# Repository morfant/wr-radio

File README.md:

# WR-Radio

## 설정 방법

### 1. 첫 실행
```bash
python3 wr-radio.py
```
첫 실행 시 `config.json` 파일이 자동 생성됩니다.

### 2. 스테이션 추가/변경
```bash
nano ~/wr-radio/config.json
```
```json
{
  "stations": [
    {
      "name": "내가 좋아하는 라디오",
      "url": "http://stream-url.mp3",
      "location": "Seoul, Korea",
      "lat": 37.5665,
      "lon": 126.9780,
      "color": [255, 100, 100]
    }
  ]
}
```

### 3. 날씨 기능 (선택)
1. https://openweathermap.org/appid 에서 무료 API 키 발급
2. `config.json`에 키 입력:
```json
   {
     "openweather_api_key": "여기에_키_입력"
   }
```

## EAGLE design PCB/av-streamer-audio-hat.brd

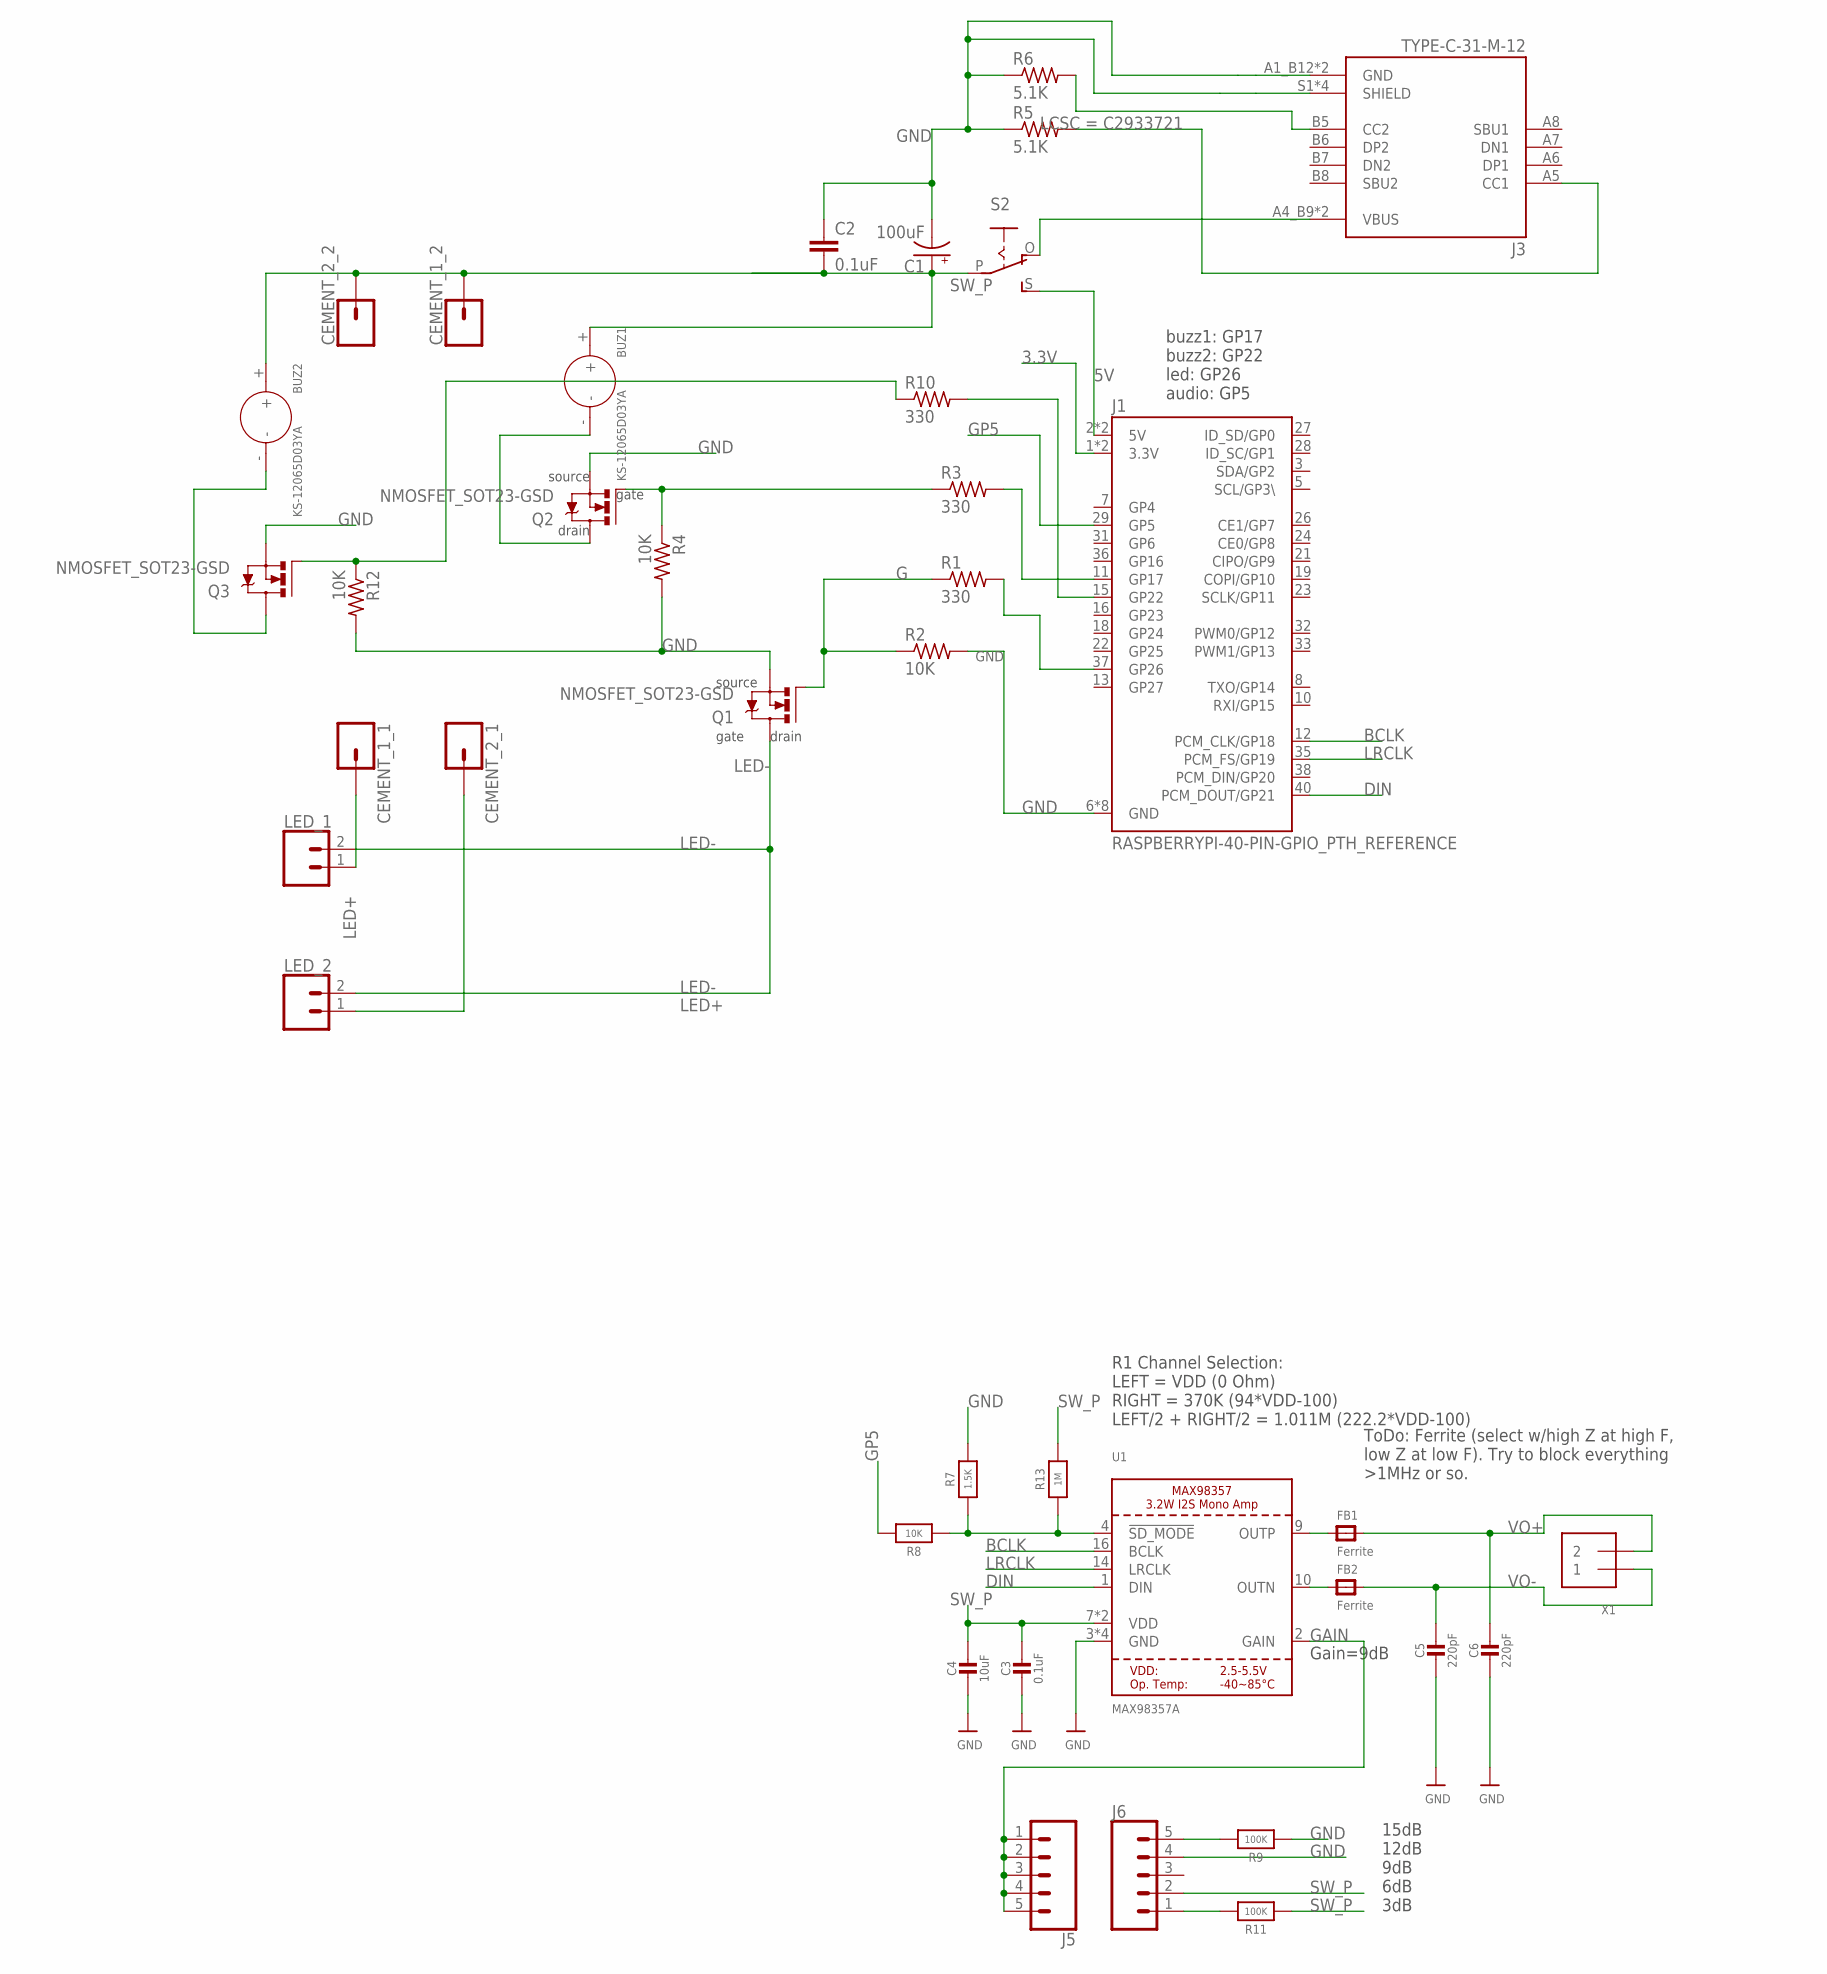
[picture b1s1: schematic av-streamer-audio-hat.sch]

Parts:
BUZ1, BUZ2: KS-12065D03YA; BZ2-7.6-D12.0XH6.5MM
C1: 100uF; EIA7343
C2: 0.1uF; 0402
C3: 0.1uF; 0805-NO
C4: 10uF; 0805-NO
C5, C6: 220pF; 0805-NO
CEMENT_1_1, CEMENT_1_2, CEMENT_2_1, CEMENT_2_2: CONN_01; 1X01
FB1, FB2: Ferrite; 0805-NO
J1: RASPBERRYPI-40-PIN-GPIO_PTH_REFERENCE; RASPBERRY_PI_HAT_40_PIN_PTH_WITH_REFERNCE
J3: TYPE-C-31-M-12; HRO_TYPE-C-31-M-12
J5, J6: CONN_05PTH; 1X05
LED_1, LED_2: CONN_02; 1X02
Q1: NMOSFET_SOT23-GSD; SOT23; LCSC C181090
Q2, Q3: NMOSFET_SOT23-GSD; SOT23
R1, R3, R10: 330; R1206
R2, R4, R12: 10K; R1206
R5, R6: 5.1K; R1206; LCSC C2933721
R7: 1.5K; 0805-NO
R8: 10K; 0805-NO
R9, R11: 100K; 0805-NO
R13: 1M; 0805-NO
S2: EG1218S; EG1218
U1: MAX98357A; QFN16_3MM
X1: TERMBLOCK_1X2; TERMBLOCK_1X2-3.5MM

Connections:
3.3V: J1.1 (3.3V), J1.17 (3.3V)
5V: J1.2 (5V), J1.4 (5V), S2.S
BCLK: J1.12 (PCM_CLK/GP18), U1.16 (BCLK)
DIN: J1.40 (PCM_DOUT/GP21), U1.1 (DIN)
G: Q1.1 (G), R1.1, R2.1
GAIN: J5.1, J5.2, J5.3, J5.4, J5.5, U1.2 (GAIN)
GND: C1.C (-), C2.1, C3.2, C4.2, C5.2, C6.2, J1.6 (GND), J1.9 (GND), J1.14 (GND), J1.20 (GND), J1.25 (GND), J1.30 (GND), J1.34 (GND), J1.39 (GND), J3.A1_B12 (GND), J3.B1_A12 (GND), J3.S1 (SHIELD), J3.S2 (SHIELD), J3.S3 (SHIELD), J3.S4 (SHIELD), J6.4, Q1.2 (S), Q2.2 (S), Q3.2 (S), R2.2, R4.2, R5.1, R6.1, R7.2, R9.1, R12.2, U1.3 (GND), U1.11 (GND), U1.15 (GND), U1.THERMAL (GND)
GP5: J1.29 (GP5), R8.2
GP16: J1.15 (GP22), R10.2
LED+: CEMENT_1_1.1, CEMENT_2_1.1, LED_1.1, LED_2.1
LED-: LED_1.2, LED_2.2, Q1.3 (D)
LRCLK: J1.35 (PCM_FS/GP19), U1.14 (LRCLK)
unnamed: J1.11 (GP17), R3.2
unnamed: FB2.1, U1.10 (OUTN)
unnamed: J1.37 (GP26), R1.2
unnamed: Q2.1 (G), R3.1, R4.1
unnamed: J3.A5 (CC1), R5.2
unnamed: J3.B5 (CC2), R6.2
unnamed: J3.A4_B9 (VBUS), J3.B4_A9 (VBUS), S2.O
unnamed: BUZ2.-, Q3.3 (D)
unnamed: BUZ1.-, Q2.3 (D)
unnamed: FB1.1, U1.9 (OUTP)
unnamed: Q3.1 (G), R10.1, R12.1
unnamed: J6.5, R9.2
unnamed: R7.1, R8.1, R13.1, U1.4 (!SD_MODE)
unnamed: J6.1, R11.2
SW_P: BUZ1.+, BUZ2.+, C1.A (+), C2.2, C3.1, C4.1, CEMENT_1_2.1, CEMENT_2_2.1, J6.2, R11.1, R13.2, S2.P, U1.7 (VDD), U1.8 (VDD)
VO+: C6.1, FB1.2, X1.2
VO-: C5.1, FB2.2, X1.1

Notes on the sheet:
source
drain
gate
R1 Channel Selection: LEFT = VDD (0 Ohm) RIGHT = 370K (94*VDD-100) LEFT/2 + RIGHT/2 = 1.011M (222.2*VDD-100)
ToDo: Ferrite (select w/high Z at high F, low Z at low F). Try to block everything >1MHz or so.
Gain=9dB
15dB 12dB 9dB 6dB 3dB
buzz1: GP17 buzz2: GP22 led: GP26 audio: GP5

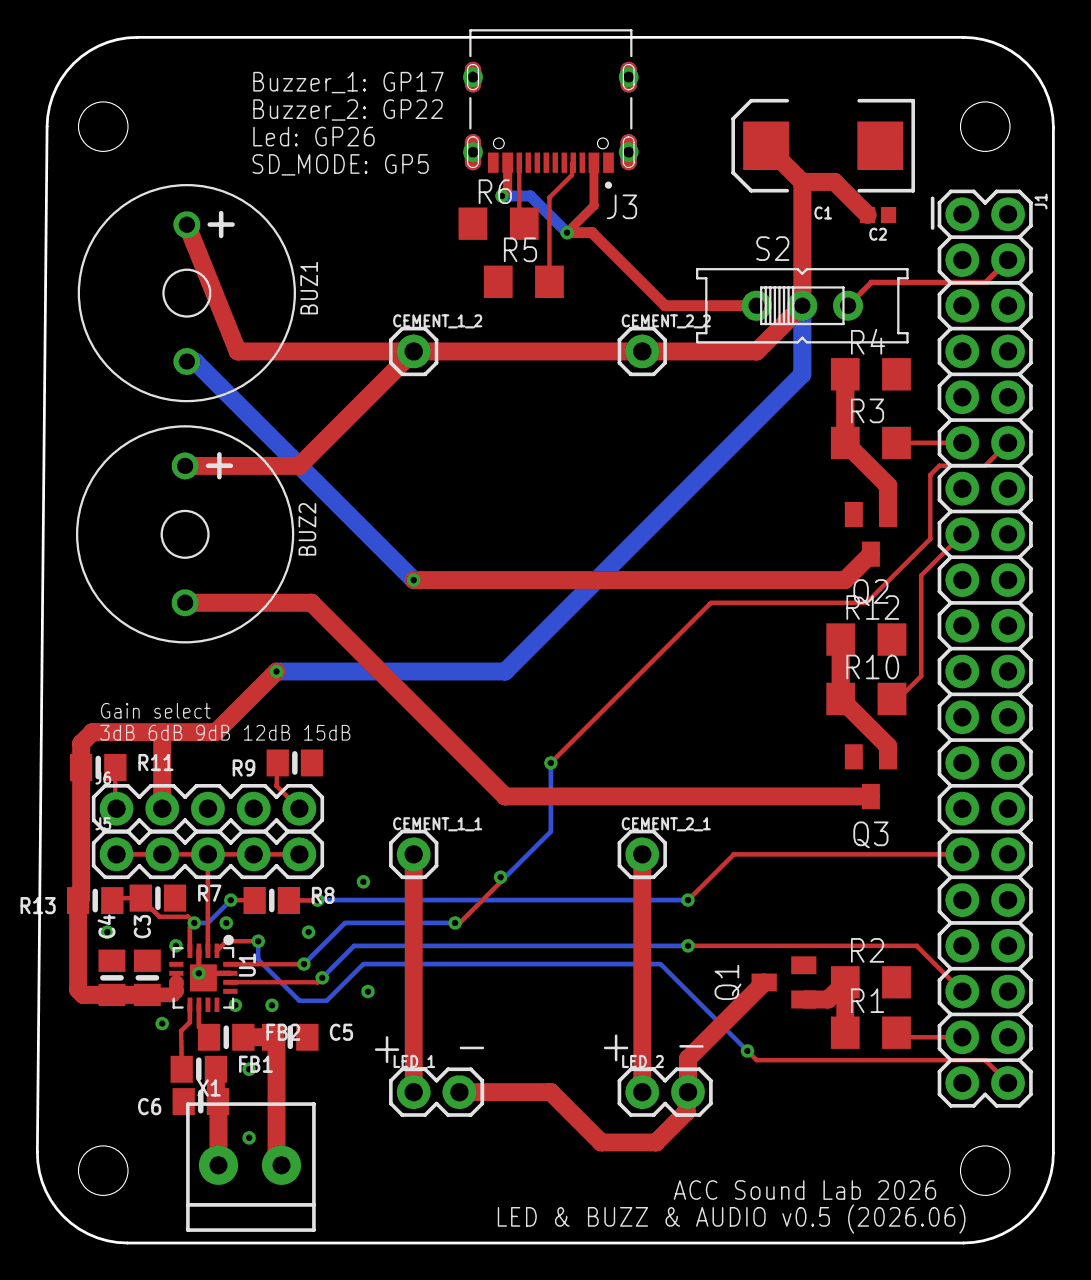
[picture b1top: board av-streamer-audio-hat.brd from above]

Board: 2 copper layers, 56.4 x 67.0 mm, 39 parts (0 on the bottom side), 29 nets.

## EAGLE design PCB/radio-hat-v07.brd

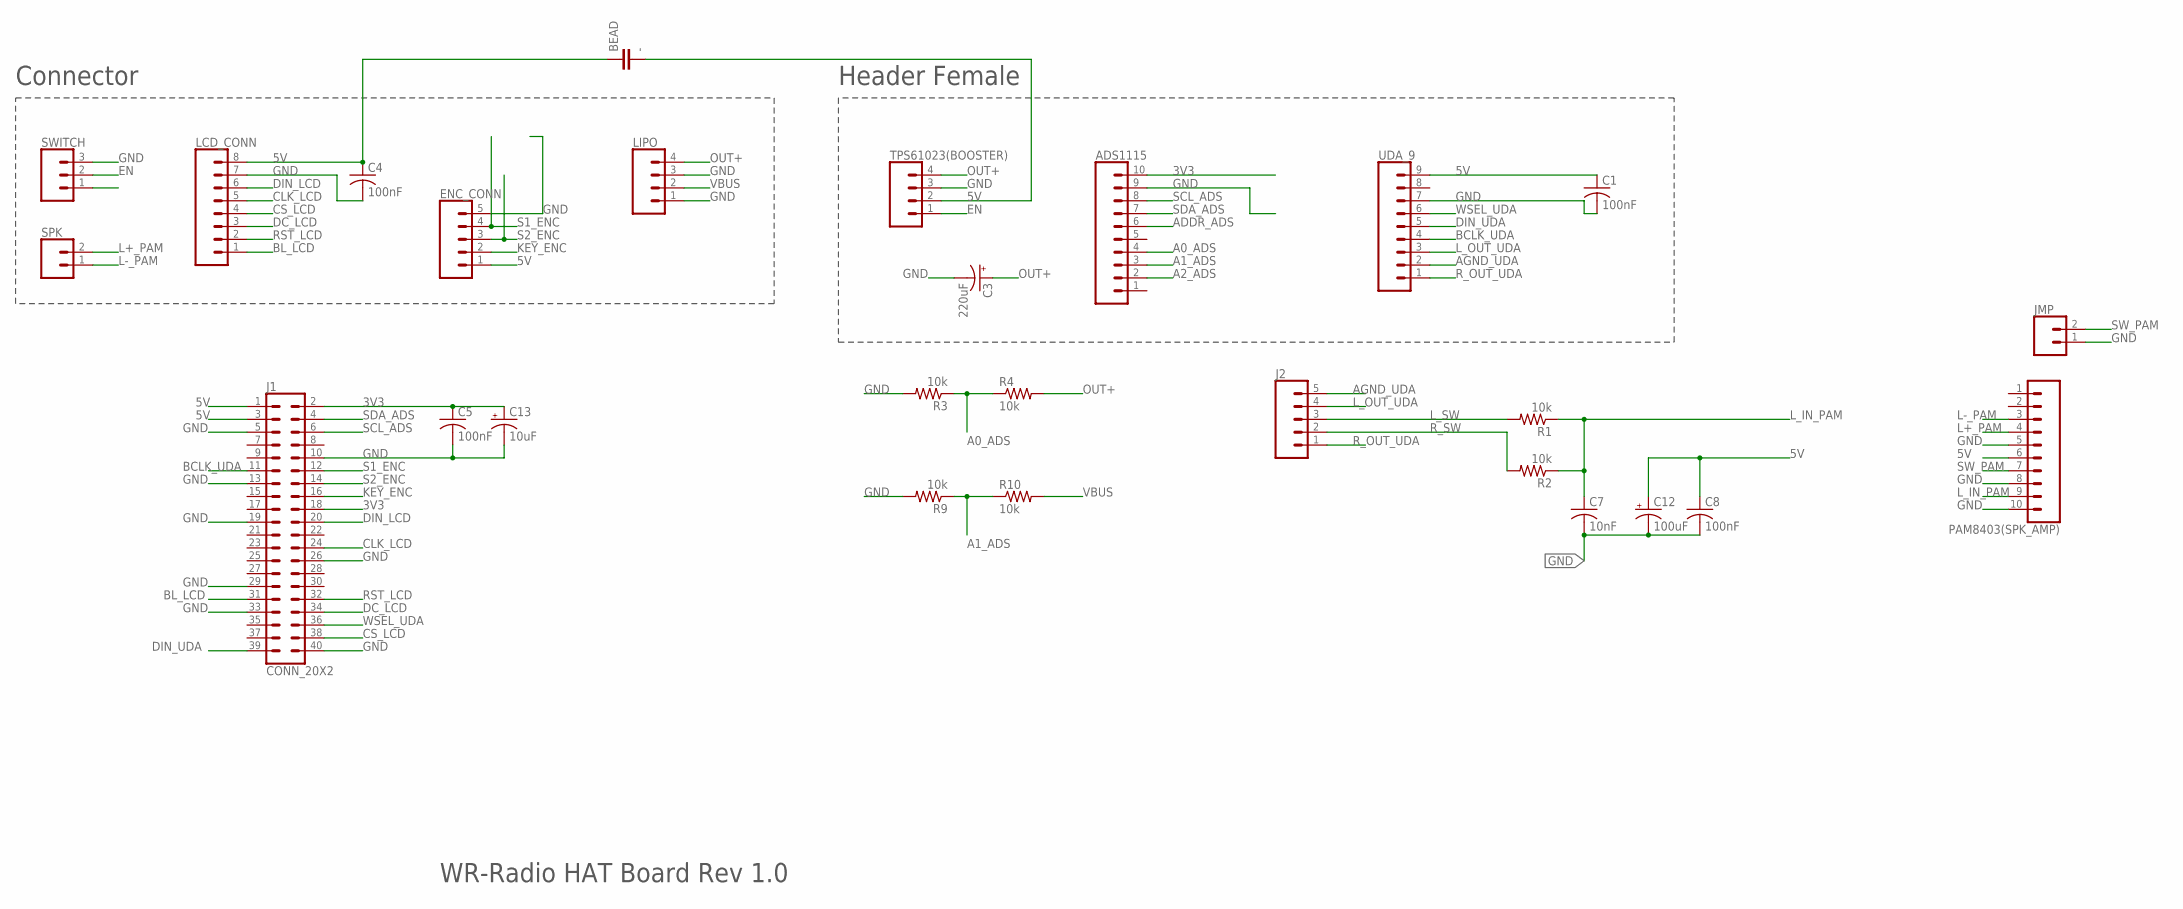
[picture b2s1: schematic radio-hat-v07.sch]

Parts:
ADS1115: CONN_10"; 1X10
BEAD: -; CAP-PTH-10MM
C1, C4, C5, C8: 100nF; C050-024X044
C3: 220uF; CPOL-RADIAL-2.5MM-6.5MM
C7: 10nF; C050-024X044
C12: 100uF; CPOL-RADIAL-2.5MM-6.5MM
C13: 10uF; CPOL-RADIAL-2.5MM-6.5MM
ENC_CONN: CONN_05PTH; 1X05
J1: CONN_20X2; 2X20
J2: CONN_05PTH; 1X05
JMP: CONN_02; 1X02
LCD_CONN: CONN_08"; 1X08
LIPO: CONN_04PTH; 1X04
PAM8403(SPK_AMP): CONN_102MM; 1X10-2MM
R1, R2, R3, R4, R9, R10: 10k; 0207/10
SPK: CONN_02; 1X02
SWITCH: CONN_03; 1X03
TPS61023(BOOSTER): CONN_04PTH; 1X04
UDA_9: CONN_09; 1X09

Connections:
3V3: ADS1115.10, C5.1, C13.1 (+), J1.2, J1.18
5V: BEAD.1, BEAD.2, C1.1, C4.1, C8.1, C12.1 (+), ENC_CONN.1, J1.1, J1.3, LCD_CONN.8 (VCC), PAM8403(SPK_AMP).6, TPS61023(BOOSTER).2, UDA_9.9
A0_ADS: ADS1115.4, R3.1, R4.1
A1_ADS: ADS1115.3, R9.1, R10.1
A2_ADS: ADS1115.2
ADDR_ADS: ADS1115.6
AGND_UDA: J2.5, UDA_9.2
BCLK_UDA: J1.11, UDA_9.4
BL_LCD: J1.31, LCD_CONN.1 (BL)
CLK_LCD: J1.24, LCD_CONN.5 (CLK)
CS_LCD: J1.38, LCD_CONN.4 (CS)
DC_LCD: J1.34, LCD_CONN.3 (DC)
DIN_LCD: J1.20, LCD_CONN.6 (DIN)
DIN_UDA: J1.39, UDA_9.5
EN: SWITCH.2, TPS61023(BOOSTER).1
GND: ADS1115.9, C1.2, C3.2 (-), C4.2, C5.2, C7.2, C8.2, C12.2 (-), C13.2 (-), ENC_CONN.5, J1.5, J1.10, J1.13, J1.19, J1.26, J1.29, J1.33, J1.40, JMP.1, LCD_CONN.7 (GND), LIPO.1, LIPO.3, PAM8403(SPK_AMP).5, PAM8403(SPK_AMP).8, PAM8403(SPK_AMP).10, R3.2, R9.2, SWITCH.3, TPS61023(BOOSTER).3, UDA_9.7
KEY_ENC: ENC_CONN.2, J1.16
L+_PAM: PAM8403(SPK_AMP).4, SPK.2
L-_PAM: PAM8403(SPK_AMP).3, SPK.1
L_IN_PAM: C7.1, PAM8403(SPK_AMP).9, R1.1, R2.1
L_OUT_UDA: J2.4, UDA_9.3
L_SW: J2.3, R1.2
OUT+: C3.1 (+), LIPO.4, R4.2, TPS61023(BOOSTER).4
RST_LCD: J1.32, LCD_CONN.2 (RST)
R_OUT_UDA: J2.1, UDA_9.1
R_SW: J2.2, R2.2
S1_ENC: ENC_CONN.4, J1.12
S2_ENC: ENC_CONN.3, J1.14
SCL_ADS: ADS1115.8, J1.6
SDA_ADS: ADS1115.7, J1.4
SW_PAM: JMP.2, PAM8403(SPK_AMP).7
VBUS: LIPO.2, R10.2
WSEL_UDA: J1.36, UDA_9.6

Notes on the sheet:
WR-Radio HAT Board Rev 1.0
Connector
Header Female

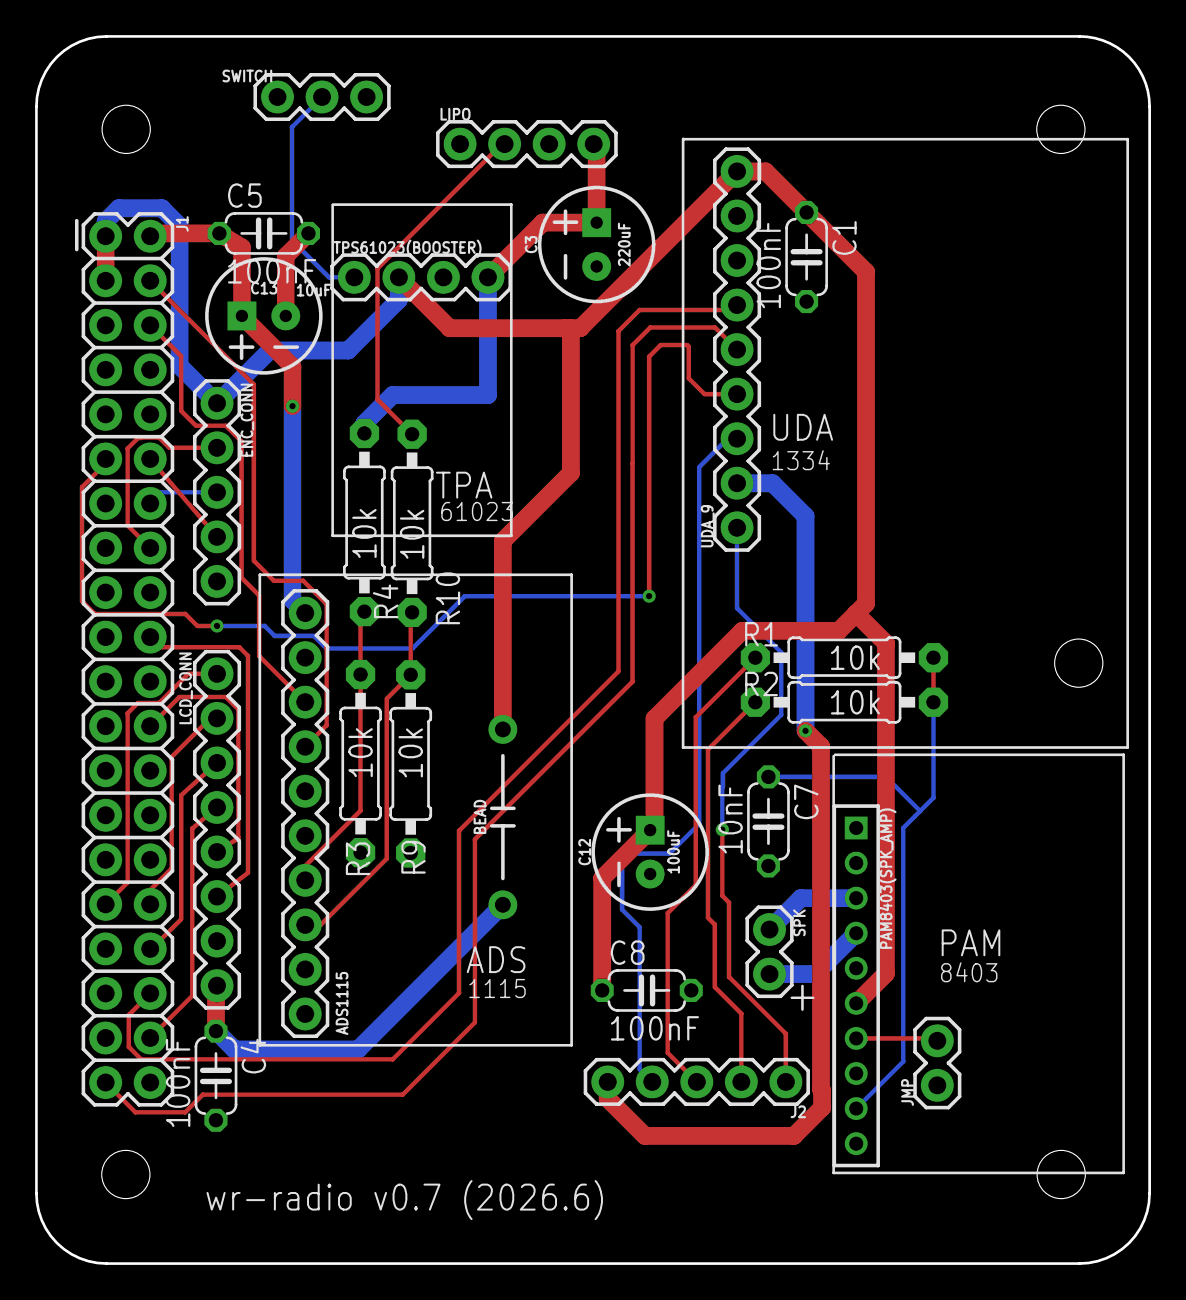
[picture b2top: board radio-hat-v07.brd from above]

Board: 2 copper layers, 63.5 x 70.0 mm, 27 parts (0 on the bottom side), 31 nets.

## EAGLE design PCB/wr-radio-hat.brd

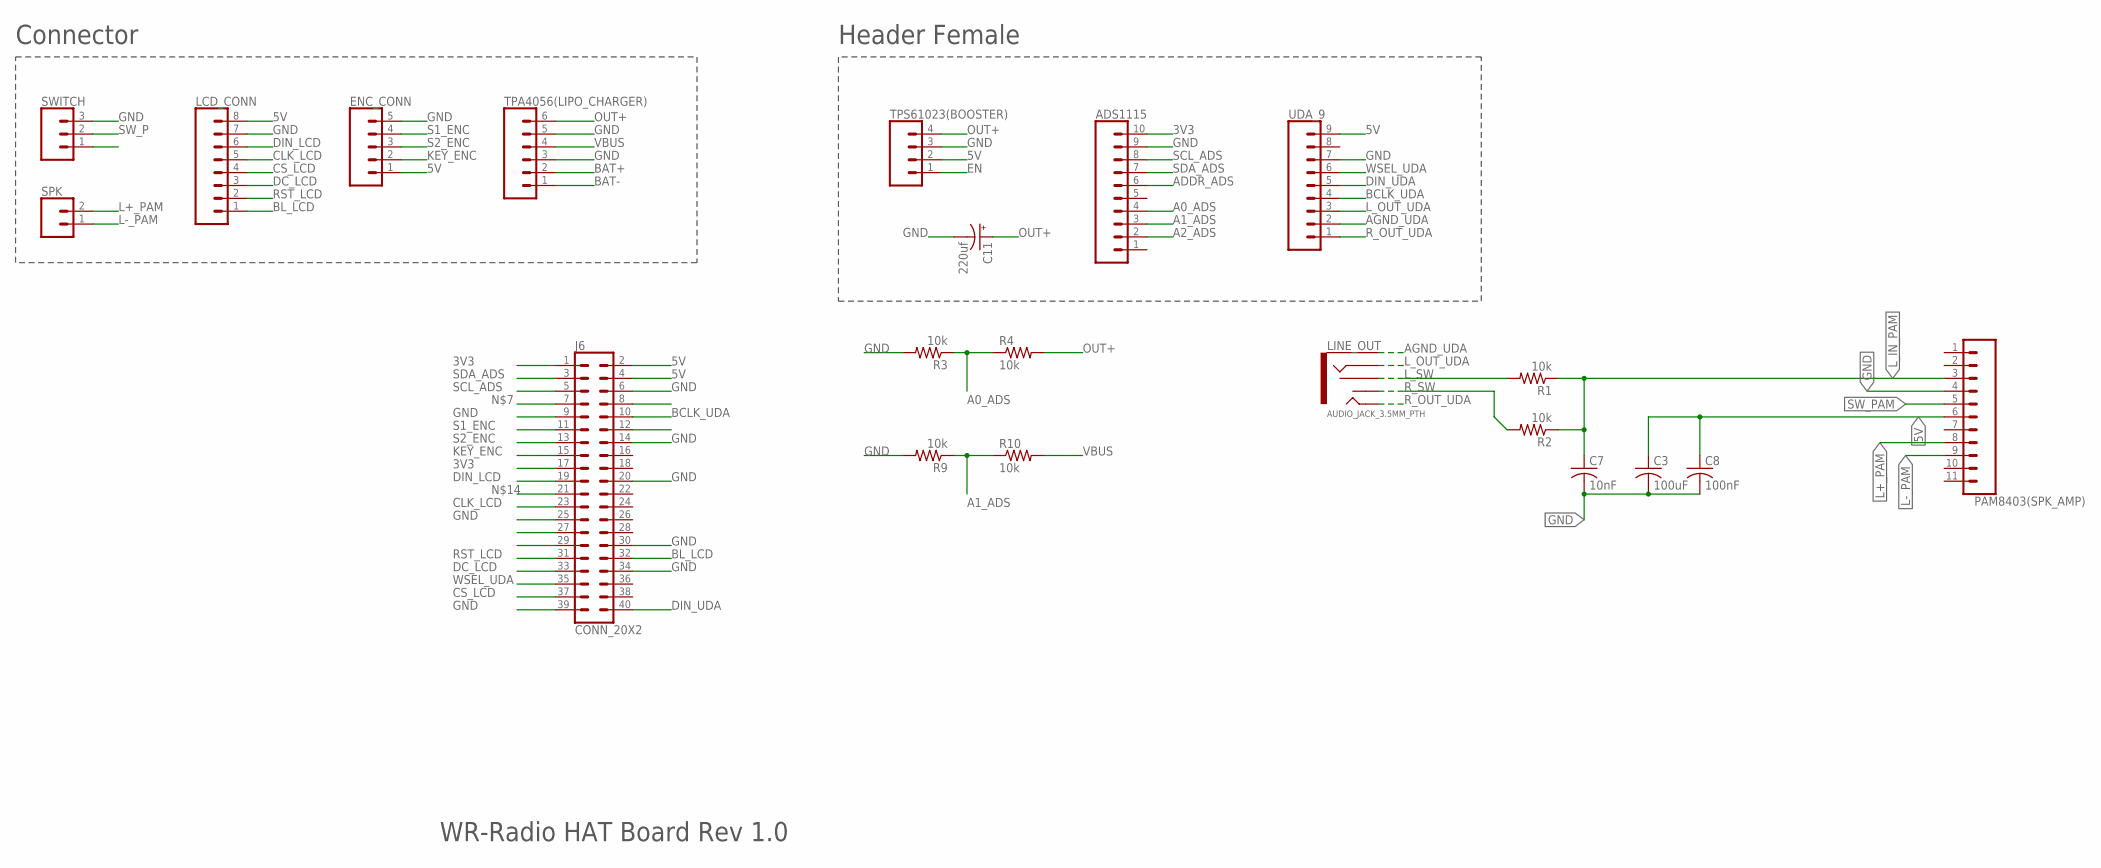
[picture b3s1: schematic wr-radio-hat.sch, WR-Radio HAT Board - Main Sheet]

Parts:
ADS1115: CONN_10"; 1X10
C3: 100uF; C050-050X075
C7: 10nF; C025-025X050
C8: 100nF; C025-025X050
C11: 220uf; E5-10,5
ENC_CONN: CONN_05PTH; 1X05
J6: CONN_20X2; 2X20
LCD_CONN: CONN_08"; 1X08
LINE_OUT: AUDIO_JACK_3.5MM_PTH; AUDIO-JACK
PAM8403(SPK_AMP): CONN_11_1.27MM; 1X11-1.27MM
R1, R2, R3, R4, R9, R10: 10k; 0207/10
SPK: CONN_02; 1X02
SWITCH: CONN_03; 1X03
TPA4056(LIPO_CHARGER): CONN_06SILK_FEMALE_PTH; 1X06
TPS61023(BOOSTER): CONN_04PTH; 1X04
UDA_9: CONN_09; 1X09

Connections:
3V3: ADS1115.10, J6.1, J6.17
5V: C3.1, C8.1, ENC_CONN.1, J6.2, J6.4, LCD_CONN.8 (VCC), PAM8403(SPK_AMP).6, TPS61023(BOOSTER).2, UDA_9.9
A0_ADS: ADS1115.4, R3.1, R4.1
A1_ADS: ADS1115.3, R9.1, R10.1
A2_ADS: ADS1115.2
ADDR_ADS: ADS1115.6
AGND_UDA: LINE_OUT.SLEEVE, UDA_9.2
BAT+: TPA4056(LIPO_CHARGER).2
BAT-: TPA4056(LIPO_CHARGER).1
BCLK_UDA: J6.10, UDA_9.4
BL_LCD: J6.32, LCD_CONN.1 (BL)
CLK_LCD: J6.23, LCD_CONN.5 (CLK)
CS_LCD: J6.37, LCD_CONN.4 (CS)
DC_LCD: J6.33, LCD_CONN.3 (DC)
DIN_LCD: J6.19, LCD_CONN.6 (DIN)
DIN_UDA: J6.40, UDA_9.5
EN: TPS61023(BOOSTER).1
GND: ADS1115.9, C3.2, C7.2, C8.2, C11.-, ENC_CONN.5, J6.6, J6.9, J6.14, J6.20, J6.25, J6.30, J6.34, J6.39, LCD_CONN.7 (GND), PAM8403(SPK_AMP).4, R3.2, R9.2, SWITCH.3, TPA4056(LIPO_CHARGER).3, TPA4056(LIPO_CHARGER).5, TPS61023(BOOSTER).3, UDA_9.7
KEY_ENC: ENC_CONN.2, J6.15
L+_PAM: PAM8403(SPK_AMP).8, SPK.2
L-_PAM: PAM8403(SPK_AMP).9, SPK.1
L_IN_PAM: C7.1, PAM8403(SPK_AMP).3, R1.1, R2.1
L_OUT_UDA: LINE_OUT.RING, UDA_9.3
L_SW: LINE_OUT.RSH, R1.2
OUT+: C11.+, R4.2, TPA4056(LIPO_CHARGER).6, TPS61023(BOOSTER).4
RST_LCD: J6.31, LCD_CONN.2 (RST)
R_OUT_UDA: LINE_OUT.TIP, UDA_9.1
R_SW: LINE_OUT.TSH, R2.2
S1_ENC: ENC_CONN.4, J6.11
S2_ENC: ENC_CONN.3, J6.13
SCL_ADS: ADS1115.8, J6.5
SDA_ADS: ADS1115.7, J6.3
SW_P: SWITCH.2
SW_PAM: PAM8403(SPK_AMP).5
VBUS: R10.2, TPA4056(LIPO_CHARGER).4
WSEL_UDA: J6.35, UDA_9.6

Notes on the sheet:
WR-Radio HAT Board Rev 1.0
Connector
Header Female

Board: 2 copper layers, 21 parts (0 on the bottom side), 29 nets, no tracks yet.

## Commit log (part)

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2026-02-02 Edit run_radio.py
2026-02-13 add lcd_test.py
2026-02-13 Add main.py
2026-02-15 edit encoder pin out
2026-02-15 Edit main.py
2026-02-15 oled test
2026-02-15 Change file name
2026-02-15 Add README, add weathre infomation
2026-02-15 Add .gitignore and config.json.example
2026-02-16 Display update, Seperate files
2026-02-16 Remove __pycache__ and pyc files
2026-02-16 Edit .gitignore
2026-02-17 Save volume and backlight. Change way to enter blt mode
2026-02-18 Loading animation
2026-02-18 Display UTC time
2026-02-18 Vol 100% display OK
2026-02-20 LCD pin change
2026-02-20 Use audio
2026-02-25 Edit EQ, Add bat_test.py
2026-02-25 Display battery status, Fix weather update timing
2026-02-25 Weather display init time change
2026-02-26 Earphone insert check system
2026-02-28 Pam 모듈 교체 후 음량 테스트
2026-02-28 Edit player.py
2026-02-28 Add some tesets
2026-02-28 Max volume = 150
2026-02-28 LCD SPI update interval change (1.0)
2026-03-02 Fix pin numbers on lcd_test.py
2026-03-02 Add boot_greeting.py
2026-03-04 Add system setting menu with long press
2026-03-04 Menu 정리
2026-03-04 첫 시작시 배터리 측정 오류 수정
2026-03-04 Edit exit message
2026-03-04 Edit shutting down message
2026-03-06 Add BT test
2026-03-06 BT 기본 기능 구현
2026-03-06 BT 기능 개선
2026-03-07 BT scan 기능 확인
2026-04-02 Add PCB files
2026-04-30 PCB v0.5 수정 후 작동 확인, note 업데이트
2026-06-29 Case modeling

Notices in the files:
parts and their libraries:
SparkFun-Connectors: Licensing: Creative Commons ShareAlike 4.0 International - https://creativecommons.org/licenses/by-sa/4.0
microbuilder: This work is placed in the public domain, and may be freely used for commercial and non-commercial work with the following conditions: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
